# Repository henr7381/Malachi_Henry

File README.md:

# Malachi Henry 
Hello and welcome to my personal Github. I am a computer engineering undergrad at Trine University.

This Github is home to my code, electrical design, and 3D models.

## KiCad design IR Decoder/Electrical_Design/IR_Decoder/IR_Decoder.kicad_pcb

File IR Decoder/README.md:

This is an IR decoder that will take input from any NEC IR based remote and display the HEX address and payload of the packet. 

I have included the code and KiCAD circuit schematic in case you want to build it yourself. It is pretty cool, and was a good way to strech my legs and write some embedded code and get some circuit design done. There are configuration notes in the code so make sure to check that out. If you use a different STM uC you'll have to recalculate timer values and swap header files. This was designed to work with STM32CUBEIDE, so I have included the main.c file for reference.

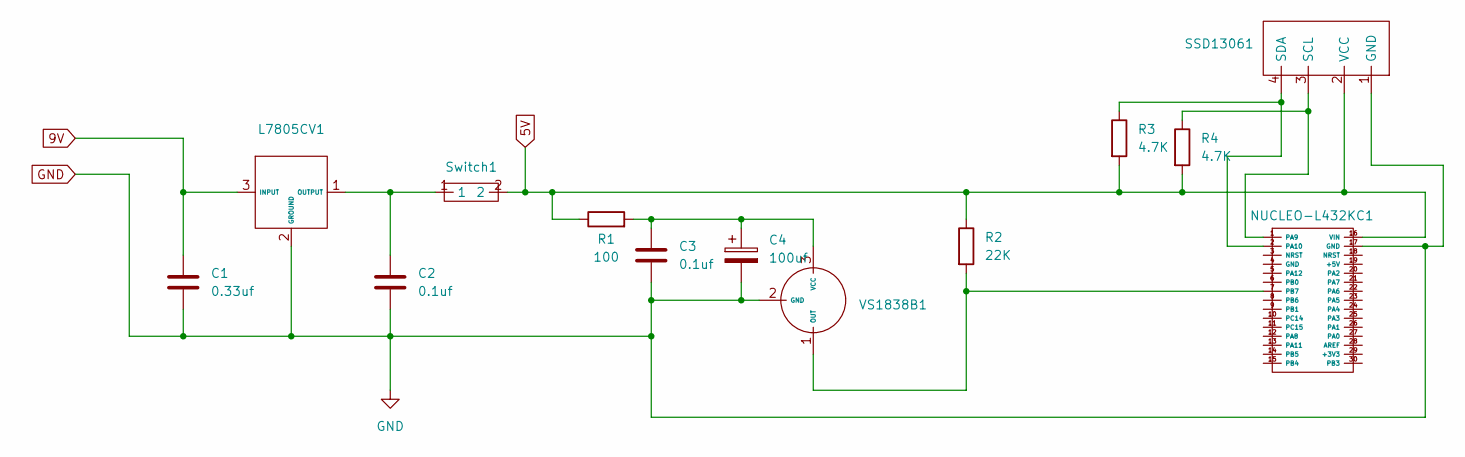
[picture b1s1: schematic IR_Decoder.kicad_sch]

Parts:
C1: 0.33uf; C_Disc_D4.3mm_W1.9mm_P5.00mm
C2, C3: 0.1uf; C_Disc_D5.0mm_W2.5mm_P2.50mm
C4: 100uf; CP_Radial_D8.0mm_P3.50mm
L7805CV1: TO-220-3_Horizontal_TabDown
NUCLEO-L432KC1: STM_Nucleo_Nano
R1: 100; R_Axial_DIN0207_L6.3mm_D2.5mm_P10.16mm_Horizontal
R2: 22K; R_Axial_DIN0204_L3.6mm_D1.6mm_P7.62mm_Horizontal
R3, R4: 4.7K; R_Axial_DIN0204_L3.6mm_D1.6mm_P7.62mm_Horizontal
SSD13061: SSD1306
Switch1: Split_with_pads
VS1838B1: Radial-3

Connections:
5V: NUCLEO-L432KC1.16 (VIN), R1.1, R2.1, R3.2, R4.2, SSD13061.2 (VCC), Switch1.2
9V: C1.1, L7805CV1.3 (INPUT); also elsewhere on the board
GND: C1.2, C2.2, C3.2, C4.2, L7805CV1.2 (GROUND), NUCLEO-L432KC1.17 (GND), SSD13061.1 (GND), VS1838B1.2 (GND); also elsewhere on the board
unnamed: C2.1, L7805CV1.1 (OUTPUT), Switch1.1
unnamed: NUCLEO-L432KC1.1 (PA9), R4.1, SSD13061.3 (SCL)
unnamed: NUCLEO-L432KC1.2 (PA10), R3.1, SSD13061.4 (SDA)
unnamed: NUCLEO-L432KC1.7 (PB7), R2.2, VS1838B1.1 (OUT)
unnamed: C3.1, C4.1, R1.2, VS1838B1.3 (VCC)

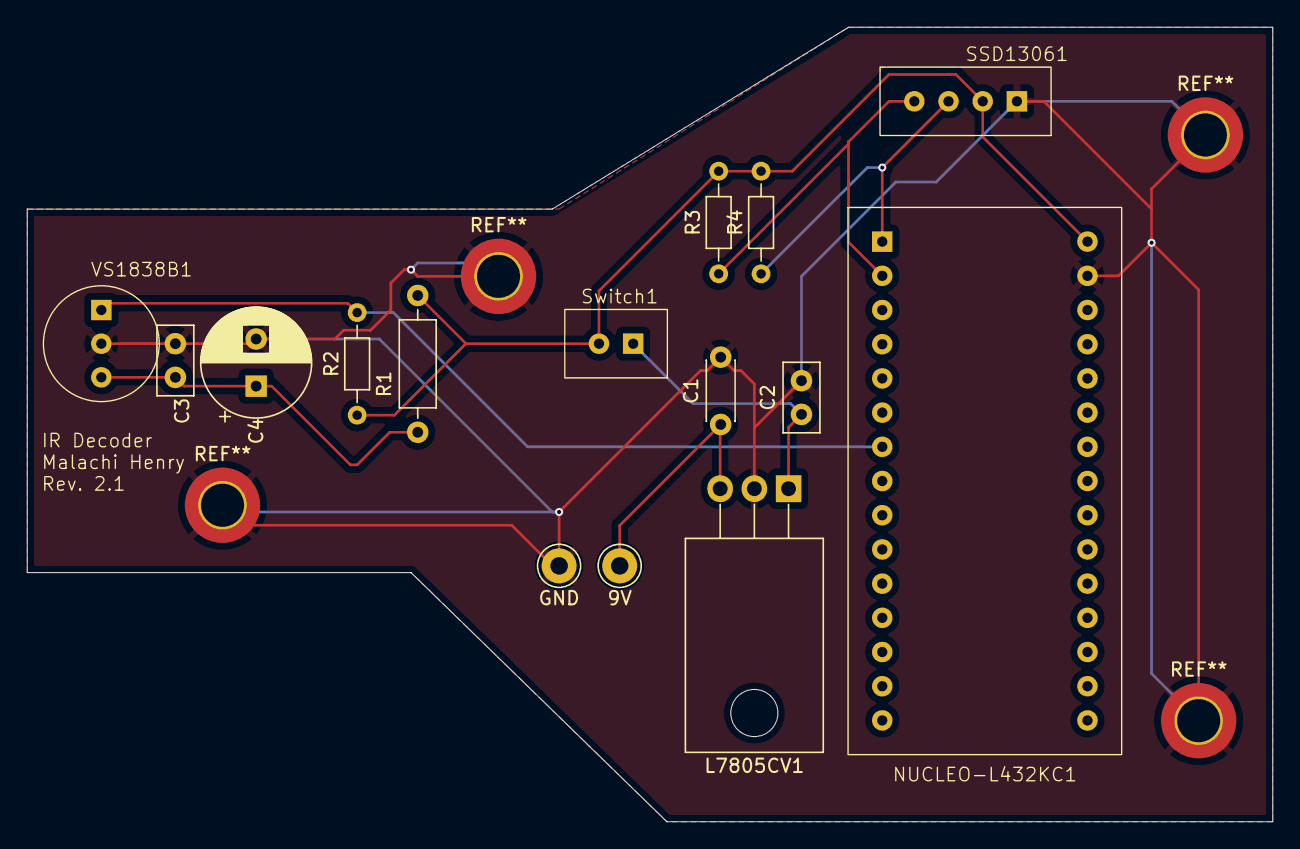
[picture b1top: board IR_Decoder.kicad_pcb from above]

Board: 2 copper layers, 92.5 x 59.0 mm, 15 parts (0 on the bottom side), 8 nets.

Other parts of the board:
9V: Pin_D1.3mm_L11.0mm
GND: Pin_D1.3mm_L11.0mm

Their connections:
9V: 9V.1; also elsewhere on the board
GND: GND.1; also elsewhere on the board

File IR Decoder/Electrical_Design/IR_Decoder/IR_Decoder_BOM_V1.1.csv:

"Reference","Value","Do Not Place","Exclude from BOM","Exclude from Board","Exclude from Simulation"
"C1","0.33uf","","","",""
"C2,C3","0.1uf","","","",""
"C4","100uf","","","",""
"L7805CV1","~","","","",""
"NUCLEO-L432KC1","~","","","",""
"R1","100","","","",""
"R2","22K","","","",""
"R3,R4","4.7K","","","",""
"SSD1","~","","","",""
"Switch1","~","","","",""
"VS1838B1","~","","","",""

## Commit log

2023-01-12 Initialization of page
    Updated license to me, and added detail to my ReadMe.
2023-01-12 Addition of BPNVG folder
    Added BPNVG folder and added a README
2023-01-12 Added mount files
    Added directory in BPNVG project and files
2023-01-12 C++ additions
    Added a location for my C++ code
2023-11-16 Added oscopeproject
2023-11-16 Fixed git within git issues
2024-01-31 Added ALU
2024-02-29 Reinit
    This is the reinit of the ALU project to the MIPS project directory
2024-04-25 Added MIPS project
2024-10-01 Project Additions 20240930
2025-08-21 Added Tracker start
